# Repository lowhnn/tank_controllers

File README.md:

# Tank controller public repository

This repository accompanies the manuscript:

Low NHN, Ng CA, Micheli F. A low-cost modular control system for multi-stressor experiments.

**Folders and files in repository:**

The *TankController* folder contains EAGLE schematic files for the tank controller shield and a parts list in the *TankControllerSchematics* subfolder and the relevant Arduino program code in the *TankControllerCode* subfolder. The *SensorCalibrationCode* subfolder contains a simple Arduino program that can be used with the tank controller units to calibrate sensors, as described in Appendix 2 of the manuscript. The *SDCardFiles* subfolder contains the list of files that should be on the microSD card used with the tank controller, and includes a readme with descriptions and instructions for all the files.

The *MasterArduino* folder contains general schematic diagrams for an implementation of the tank controllers in an experimental aquaria system, including an ethernet-connected 'Master' Arduino board that consolidates data from multiple tanks and sends them to online datastreams via the [ThingSpeak](http://thingspeak.com) platform. The *UABC_MasterCode* subfolder contains the Arduino program code for running such a Master board.

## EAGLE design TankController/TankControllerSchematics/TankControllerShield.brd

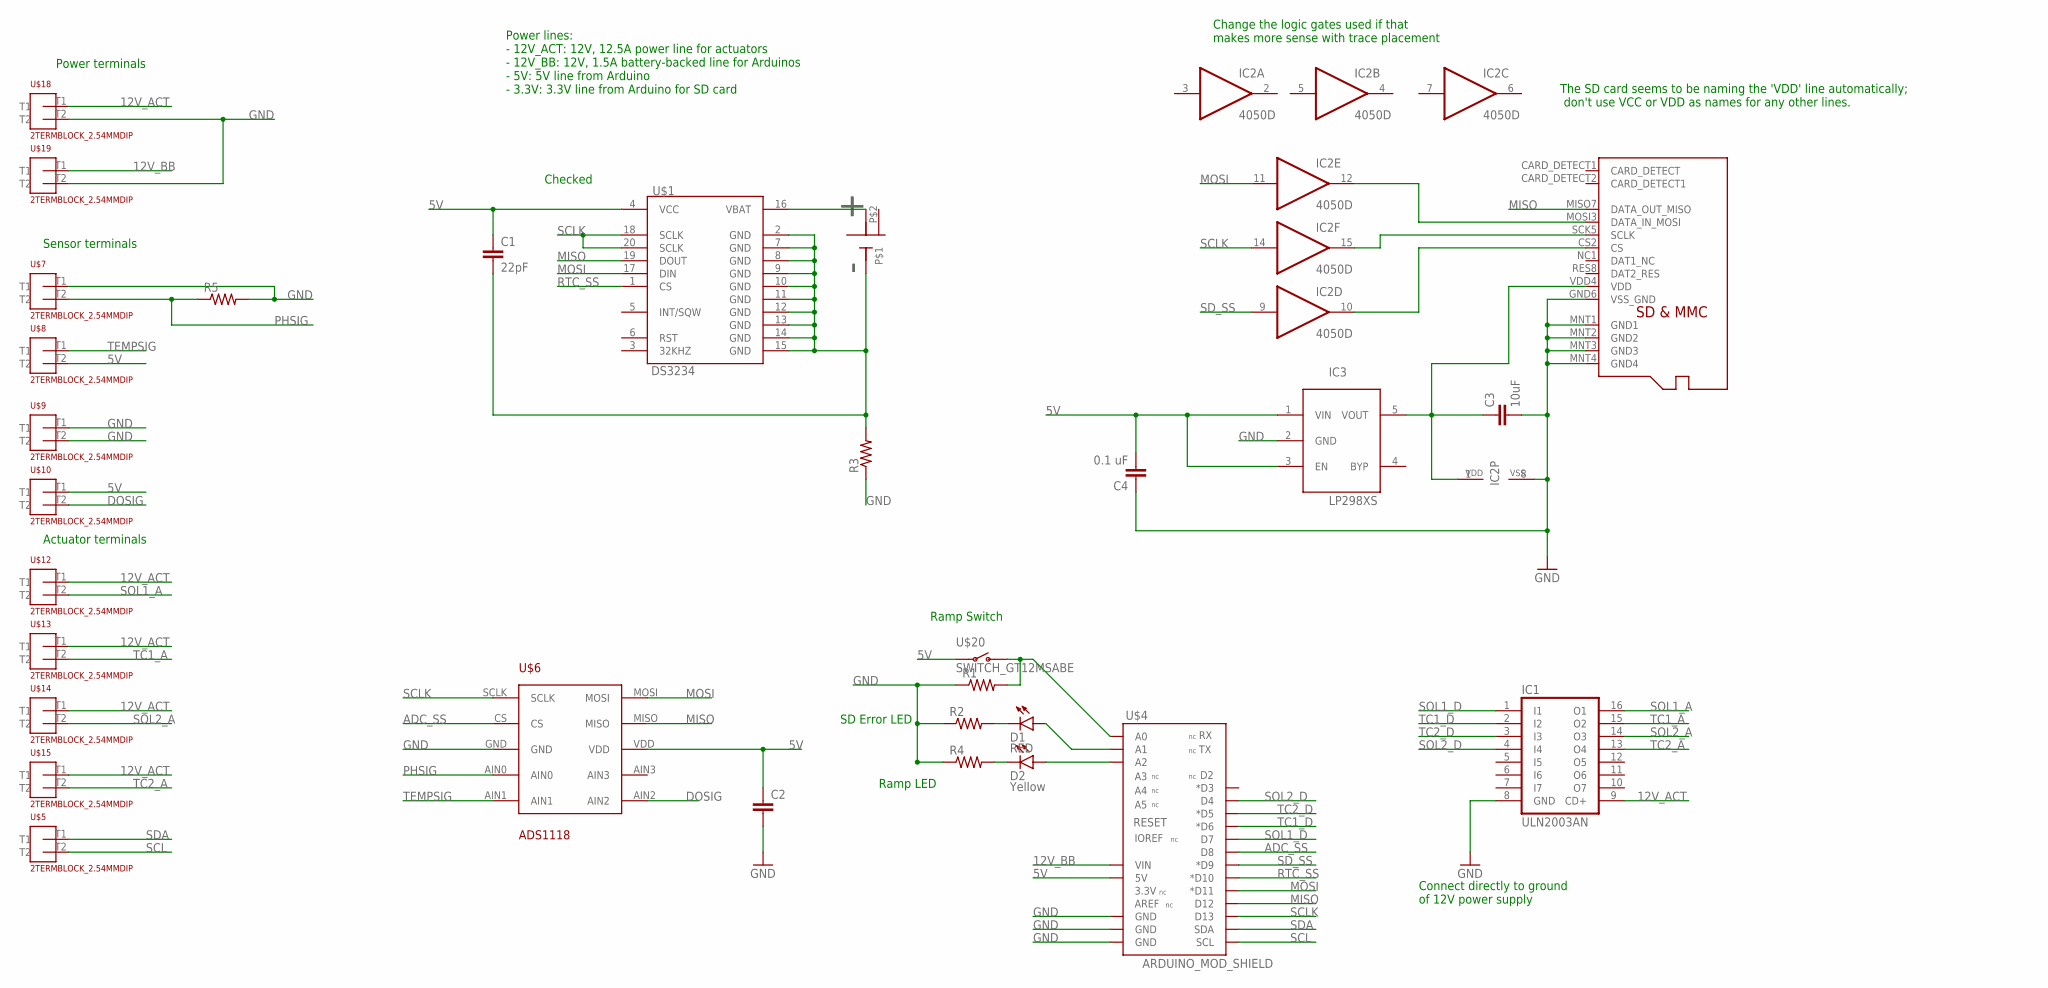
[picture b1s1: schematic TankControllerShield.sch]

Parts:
C1: 22pF; 0603-CAP
C2: CAP0603-CAP; 0603-CAP
C3: 10uF; 0603-CAP
C4: 0.1 uF; 0603-CAP
D1: RED; LED-0603
D2: Yellow; LED-0603
IC1: ULN2003AN; DIL16
IC2: 4050D; SO16
IC3: LP298XS; SOT23-5L
R1, R2, R3, R4, R5: RESISTOR0603-RES; 0603-RES
U$1: DS3234
U$2: CR1220_BATTERY_HOLDERSMD; CR1220_BATTERY_HOLDER_SMD
U$3: MICROSD_MOLEX_REVERSE; MICROSD_SOCKET_MOLEX_REVERSEMOUNT
U$4: ARDUINO_MOD_SHIELD; UNO_MOD_SHIELD
U$5, U$7, U$8, U$9, U$10, U$12, U$13, U$14, U$15, U$18, U$19: 2TERMBLOCK_2.54MMDIP; 2TERMBLOCK_2.54MM
U$6: ADS1118
U$20: SWITCH_GT12MSABE; TOGGLESWITCH

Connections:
3V: C3.1, IC2.1 (VDD), IC3.5 (VOUT), U$3.VDD4 (VDD)
5V: C1.1, C2.1, C4.2, IC3.1 (VIN), IC3.3 (EN), U$1.4 (VCC), U$4.5V, U$6.VDD, U$8.T2, U$10.T1, U$20.1
12V_ACT: IC1.9 (CD+), U$12.T1, U$13.T1, U$14.T1, U$15.T1, U$18.T1
12V_BB: U$4.VIN, U$19.T1
ADC_SS: U$4.D8, U$6.CS
DOSIG: U$6.AIN2, U$10.T2
GND: C2.2, C3.2, C4.1, IC1.8 (GND), IC2.8 (VSS), IC3.2 (GND), R1.1, R2.1, R3.1, R4.1, R5.2, U$3.GND6 (VSS_GND), U$3.MNT1 (GND1), U$3.MNT2 (GND2), U$3.MNT3 (GND3), U$3.MNT4 (GND4), U$4.GND@0 (GND), U$4.GND@1 (GND), U$4.GND@2 (GND), U$6.GND, U$7.T1, U$9.T1, U$9.T2, U$18.T2, U$19.T2
MISO: U$1.19 (DOUT), U$3.MISO7 (DATA_OUT_MISO), U$4.D12, U$6.MISO
MOSI: IC2.11 (I), U$1.17 (DIN), U$4.D11 (*D11), U$6.MOSI
unnamed: U$1.16 (VBAT), U$2.P$1 (VBAT)
unnamed: IC2.12 (O), U$3.MOSI3 (DATA_IN_MOSI)
unnamed: IC2.15 (O), U$3.SCK5 (SCLK)
unnamed: IC2.10 (O), U$3.CS2 (CS)
unnamed: D1.A, U$4.A1
unnamed: D2.A, U$4.A2
unnamed: D1.C, R2.2
unnamed: C1.2, R3.2, U$1.2 (GND), U$1.7 (GND), U$1.8 (GND), U$1.9 (GND), U$1.10 (GND), U$1.11 (GND), U$1.12 (GND), U$1.13 (GND), U$1.14 (GND), U$1.15 (GND), U$2.GND
unnamed: D2.C, R4.2
unnamed: R1.2, U$4.A0, U$20.3
PHSIG: R5.1, U$6.AIN0, U$7.T2
RTC_SS: U$1.1 (CS), U$4.D10 (*D10)
SCL: U$4.SCL, U$5.T2
SCLK: IC2.14 (I), U$1.18 (SCLK), U$1.20 (SCLK), U$4.D13, U$6.SCLK
SDA: U$4.SDA, U$5.T1
SD_SS: IC2.9 (I), U$4.D9 (*D9)
SOL1_A: IC1.16 (O1), U$12.T2
SOL1_D: IC1.1 (I1), U$4.D7
SOL2_A: IC1.14 (O3), U$14.T2
SOL2_D: IC1.4 (I4), U$4.D4
TC1_A: IC1.15 (O2), U$13.T2
TC1_D: IC1.2 (I2), U$4.D6 (*D6)
TC2_A: IC1.13 (O4), U$15.T2
TC2_D: IC1.3 (I3), U$4.D5 (*D5)
TEMPSIG: U$6.AIN1, U$8.T1

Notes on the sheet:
Connect directly to ground of 12V power supply
Change the logic gates used if that makes more sense with trace placement
The SD card seems to be naming the 'VDD' line automatically; don't use VCC or VDD as names for any other lines.
Power terminals
Sensor terminals
Actuator terminals
Power lines: - 12V_ACT: 12V, 12.5A power line for actuators - 12V_BB: 12V, 1.5A battery-backed line for Arduinos - 5V: 5V line from Arduino - 3.3V: 3.3V line from Arduino for SD card
Checked
Ramp Switch
SD Error LED
Ramp LED

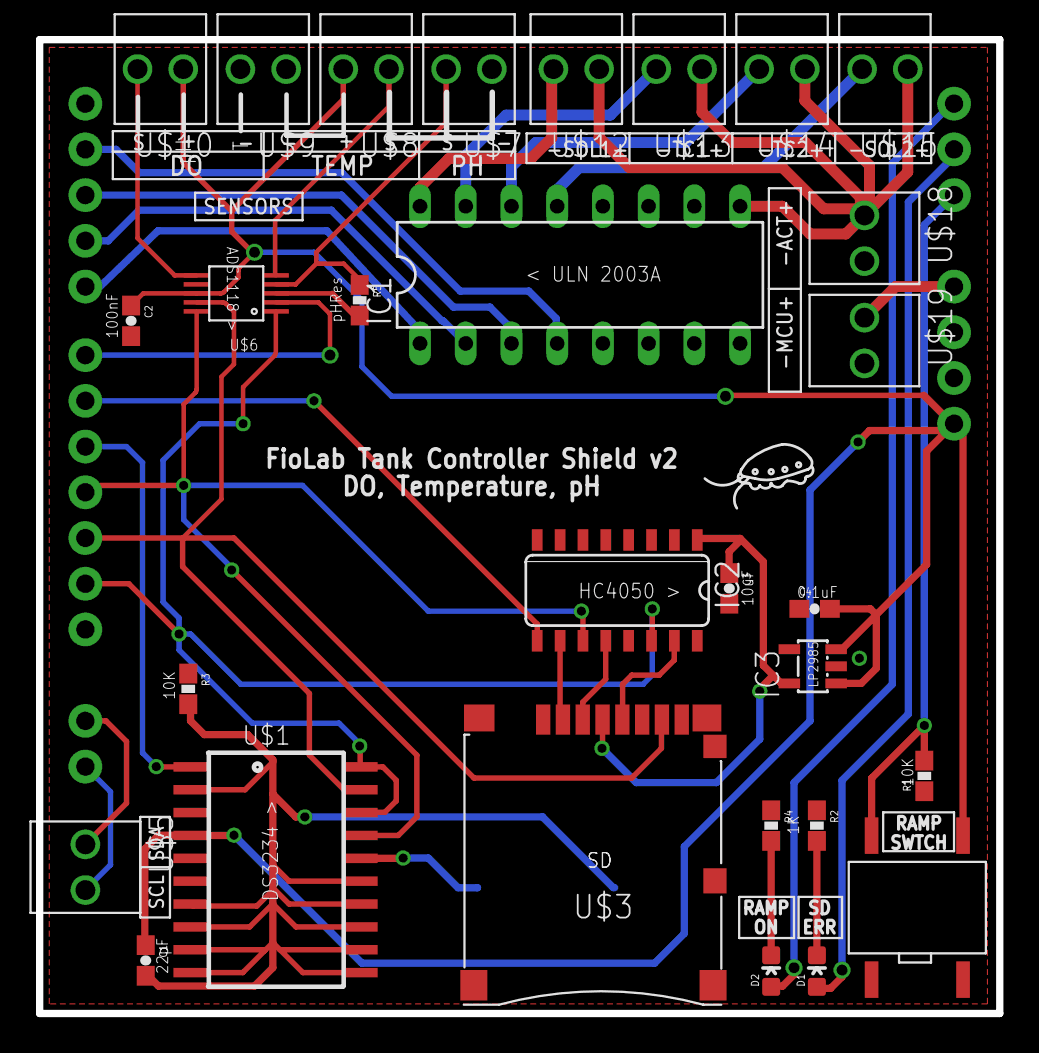
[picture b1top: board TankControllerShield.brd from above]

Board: 2 copper layers, 53.3 x 54.1 mm, 31 parts (1 on the bottom side), 34 nets.

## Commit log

2019-10-21 sample sd card files
2019-10-21 updated description
2019-10-21 schematics
2020-03-17 update paper title
